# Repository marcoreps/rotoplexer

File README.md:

# rotoplexer
 Nanovolt scanner with rotary switches, first draft for experimentation only

Inspired by
https://dataproof.com/Publications/NBS430.PDF
https://iopscience.iop.org/article/10.1088/0957-0233/24/2/025008

Python software example
https://github.com/marcoreps/multiinstrumentalist/blob/11b641b6d90bda38c73909955b253200de4179e4/main.py#L624

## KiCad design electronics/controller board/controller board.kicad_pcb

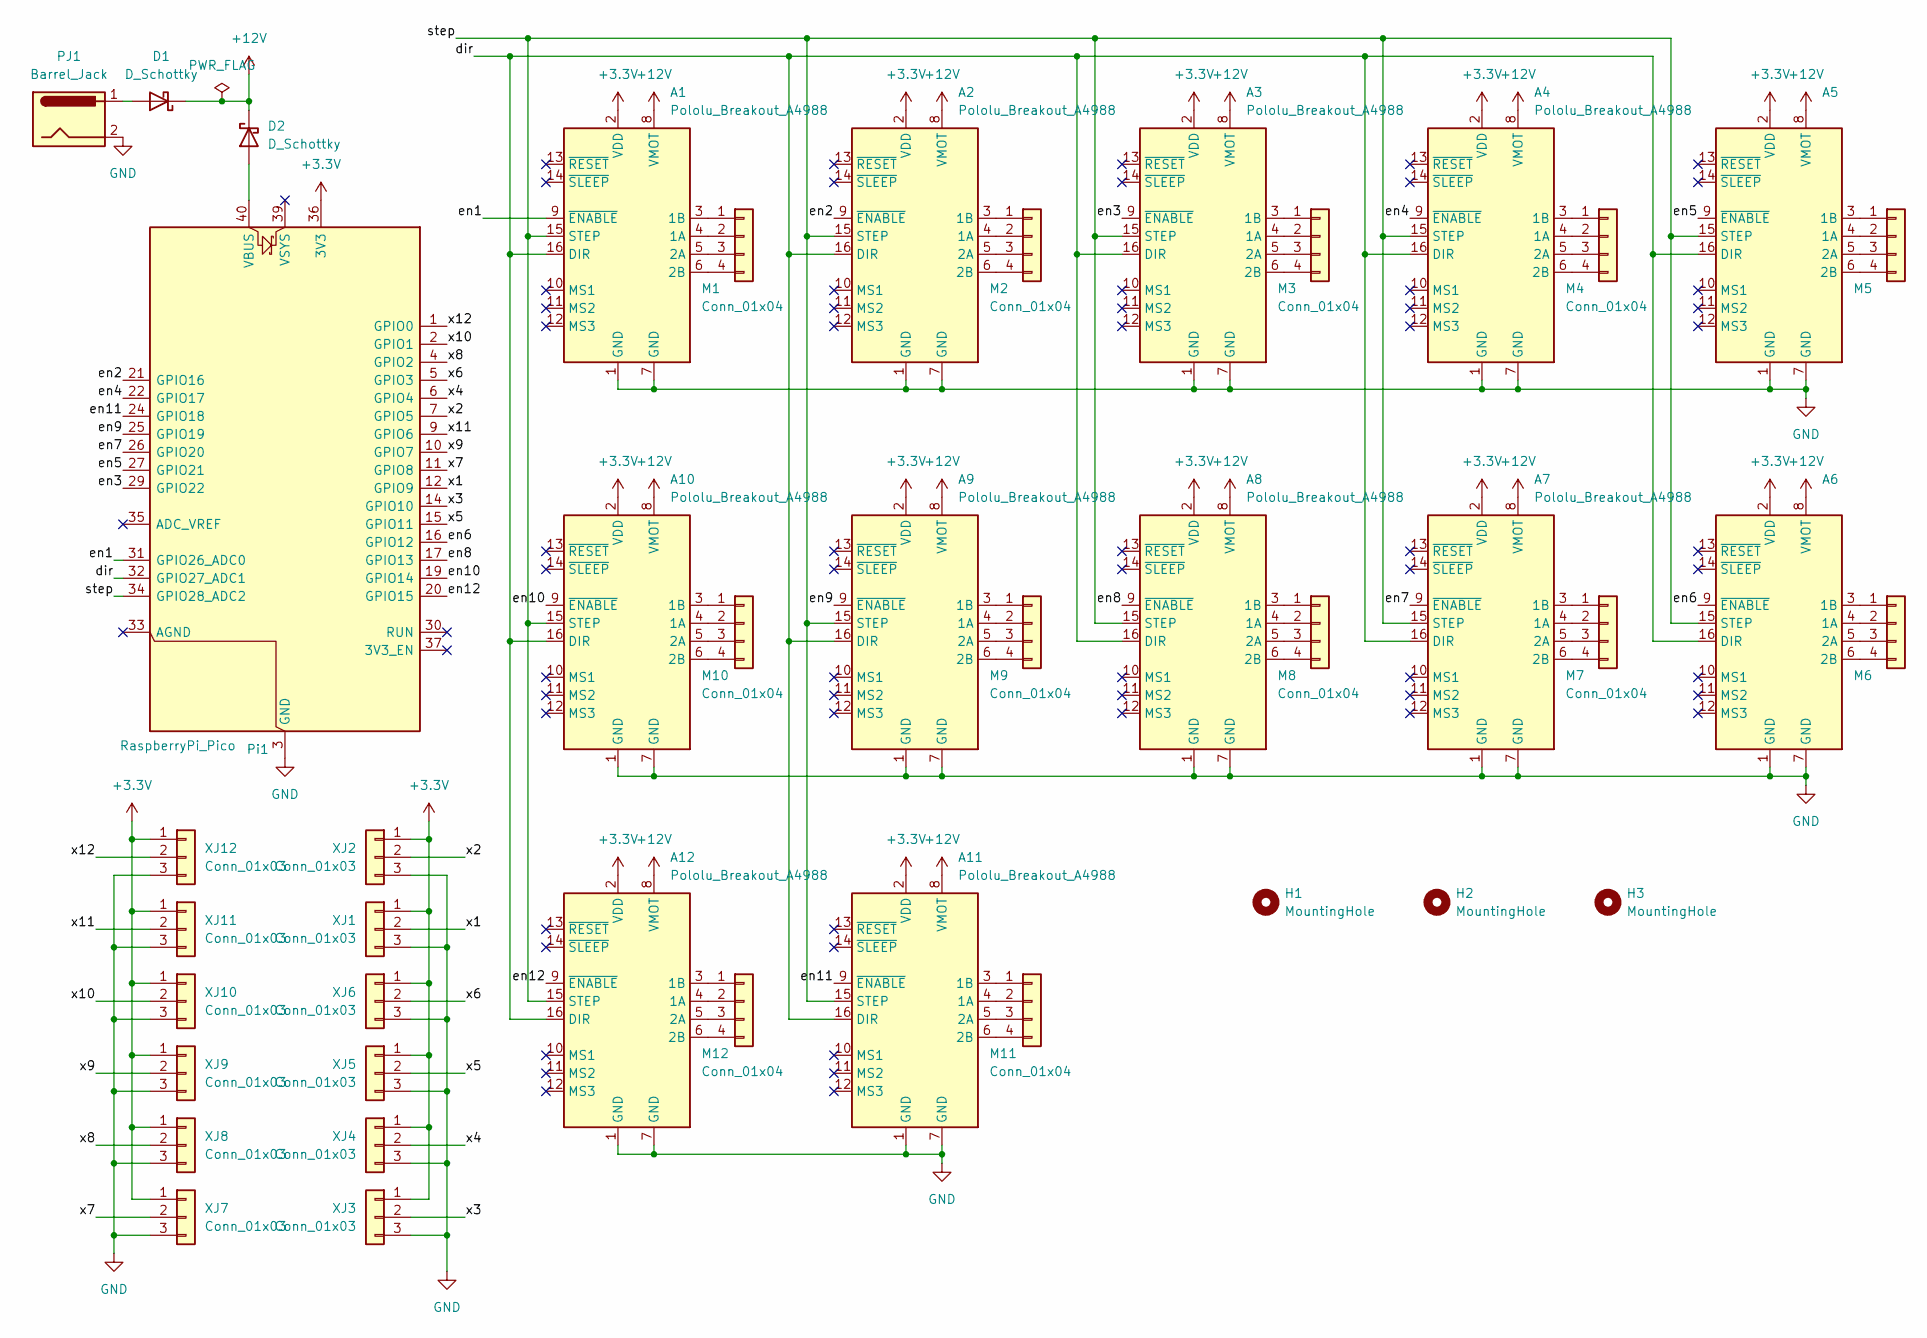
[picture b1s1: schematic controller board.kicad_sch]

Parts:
A1, A2, A3, A4, A5, A6, A7, A8, A9, A10, A11, A12: Pololu_Breakout_A4988; Pololu_Breakout-16_15.2x20.3mm
D1, D2: D_Schottky; D_SMA
H1, H2, H3: MountingHole; MountingHole_3.2mm_M3
M1, M2, M3, M4, M5, M6, M7, M8, M9, M10, M11, M12: Conn_01x04; PinHeader_1x04_P2.54mm_Vertical
PJ1: Barrel_Jack; BarrelJack_CUI_PJ-063AH_Horizontal
Pi1: RaspberryPi_Pico; RaspberryPi_Pico_Common
XJ1, XJ2, XJ3, XJ4, XJ5, XJ6, XJ7, XJ8, XJ9, XJ10, XJ11, XJ12: Conn_01x03; PinHeader_1x03_P2.54mm_Vertical

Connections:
+3.3V: A1.2 (VDD), A2.2 (VDD), A3.2 (VDD), A4.2 (VDD), A5.2 (VDD), A6.2 (VDD), A7.2 (VDD), A8.2 (VDD), A9.2 (VDD), A10.2 (VDD), A11.2 (VDD), A12.2 (VDD), Pi1.36 (3V3), XJ1.1, XJ2.1, XJ3.1, XJ4.1, XJ5.1, XJ6.1, XJ7.1, XJ8.1, XJ9.1, XJ10.1, XJ11.1, XJ12.1
+12V: A1.8 (VMOT), A2.8 (VMOT), A3.8 (VMOT), A4.8 (VMOT), A5.8 (VMOT), A6.8 (VMOT), A7.8 (VMOT), A8.8 (VMOT), A9.8 (VMOT), A10.8 (VMOT), A11.8 (VMOT), A12.8 (VMOT), D1.1 (K), D2.1 (K)
/dir: A1.16 (DIR), A2.16 (DIR), A3.16 (DIR), A4.16 (DIR), A5.16 (DIR), A6.16 (DIR), A7.16 (DIR), A8.16 (DIR), A9.16 (DIR), A10.16 (DIR), A11.16 (DIR), A12.16 (DIR), Pi1.32 (GPIO27_ADC1)
/en1: A1.9 (~ENABLE), Pi1.31 (GPIO26_ADC0)
/en2: A2.9 (~ENABLE), Pi1.21 (GPIO16)
/en3: A3.9 (~ENABLE), Pi1.29 (GPIO22)
/en4: A4.9 (~ENABLE), Pi1.22 (GPIO17)
/en5: A5.9 (~ENABLE), Pi1.27 (GPIO21)
/en6: A6.9 (~ENABLE), Pi1.16 (GPIO12)
/en7: A7.9 (~ENABLE), Pi1.26 (GPIO20)
/en8: A8.9 (~ENABLE), Pi1.17 (GPIO13)
/en9: A9.9 (~ENABLE), Pi1.25 (GPIO19)
/en10: A10.9 (~ENABLE), Pi1.19 (GPIO14)
/en11: A11.9 (~ENABLE), Pi1.24 (GPIO18)
/en12: A12.9 (~ENABLE), Pi1.20 (GPIO15)
/step: A1.15 (STEP), A2.15 (STEP), A3.15 (STEP), A4.15 (STEP), A5.15 (STEP), A6.15 (STEP), A7.15 (STEP), A8.15 (STEP), A9.15 (STEP), A10.15 (STEP), A11.15 (STEP), A12.15 (STEP), Pi1.34 (GPIO28_ADC2)
/x1: Pi1.12 (GPIO9), XJ1.2
/x2: Pi1.7 (GPIO5), XJ2.2
/x3: Pi1.14 (GPIO10), XJ3.2
/x4: Pi1.6 (GPIO4), XJ4.2
/x5: Pi1.15 (GPIO11), XJ5.2
/x6: Pi1.5 (GPIO3), XJ6.2
/x7: Pi1.11 (GPIO8), XJ7.2
/x8: Pi1.4 (GPIO2), XJ8.2
/x9: Pi1.10 (GPIO7), XJ9.2
/x10: Pi1.2 (GPIO1), XJ10.2
/x11: Pi1.9 (GPIO6), XJ11.2
/x12: Pi1.1 (GPIO0), XJ12.2
GND: A1.1 (GND), A1.7 (GND), A2.1 (GND), A2.7 (GND), A3.1 (GND), A3.7 (GND), A4.1 (GND), A4.7 (GND), A5.1 (GND), A5.7 (GND), A6.1 (GND), A6.7 (GND), A7.1 (GND), A7.7 (GND), A8.1 (GND), A8.7 (GND), A9.1 (GND), A9.7 (GND), A10.1 (GND), A10.7 (GND), A11.1 (GND), A11.7 (GND), A12.1 (GND), A12.7 (GND), PJ1.2, Pi1.3 (GND), Pi1.8 (GND), Pi1.13 (GND), Pi1.18 (GND), Pi1.23 (GND), Pi1.28 (GND), Pi1.38 (GND), XJ1.3, XJ2.3, XJ3.3, XJ4.3, XJ5.3, XJ6.3, XJ7.3, XJ8.3, XJ9.3, XJ10.3, XJ11.3, XJ12.3
unnamed: A1.4 (1A), M1.2
unnamed: A1.3 (1B), M1.1
unnamed: A1.5 (2A), M1.3
unnamed: A1.6 (2B), M1.4
unnamed: A2.4 (1A), M2.2
unnamed: A2.3 (1B), M2.1
unnamed: A2.5 (2A), M2.3
unnamed: A2.6 (2B), M2.4
unnamed: A3.4 (1A), M3.2
unnamed: A3.3 (1B), M3.1
unnamed: A3.5 (2A), M3.3
unnamed: A3.6 (2B), M3.4
unnamed: A4.4 (1A), M4.2
unnamed: A4.3 (1B), M4.1
unnamed: A4.5 (2A), M4.3
unnamed: A4.6 (2B), M4.4
unnamed: A5.4 (1A), M5.2
unnamed: A5.3 (1B), M5.1
unnamed: A5.5 (2A), M5.3
unnamed: A5.6 (2B), M5.4
unnamed: A6.4 (1A), M6.2
unnamed: A6.3 (1B), M6.1
unnamed: A6.5 (2A), M6.3
unnamed: A6.6 (2B), M6.4
unnamed: A7.4 (1A), M7.2
unnamed: A7.3 (1B), M7.1
unnamed: A7.5 (2A), M7.3
unnamed: A7.6 (2B), M7.4
unnamed: A8.4 (1A), M8.2
unnamed: A8.3 (1B), M8.1
unnamed: A8.5 (2A), M8.3
unnamed: A8.6 (2B), M8.4
unnamed: A9.4 (1A), M9.2
unnamed: A9.3 (1B), M9.1
unnamed: A9.5 (2A), M9.3
unnamed: A9.6 (2B), M9.4
unnamed: A10.4 (1A), M10.2
unnamed: A10.3 (1B), M10.1
unnamed: A10.5 (2A), M10.3
unnamed: A10.6 (2B), M10.4
unnamed: A11.4 (1A), M11.2
unnamed: A11.3 (1B), M11.1
unnamed: A11.5 (2A), M11.3
unnamed: A11.6 (2B), M11.4
unnamed: A12.4 (1A), M12.2
unnamed: A12.3 (1B), M12.1
unnamed: A12.5 (2A), M12.3
unnamed: A12.6 (2B), M12.4
unnamed: D1.2 (A), PJ1.1
unnamed: D2.2 (A), Pi1.40 (VBUS)

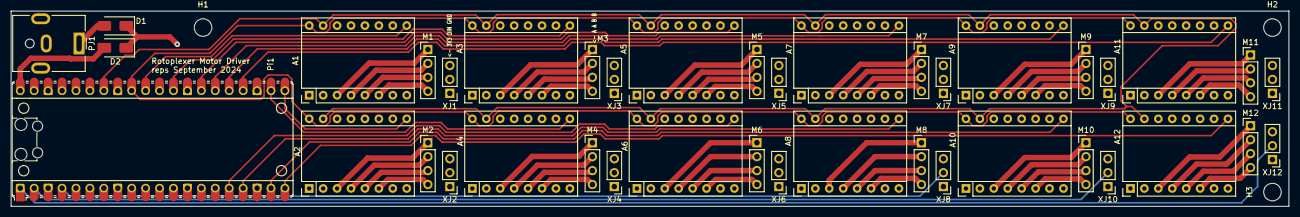
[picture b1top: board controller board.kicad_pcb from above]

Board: 4 copper layers, 233.0 x 35.6 mm, 43 parts (0 on the bottom side), 79 nets.

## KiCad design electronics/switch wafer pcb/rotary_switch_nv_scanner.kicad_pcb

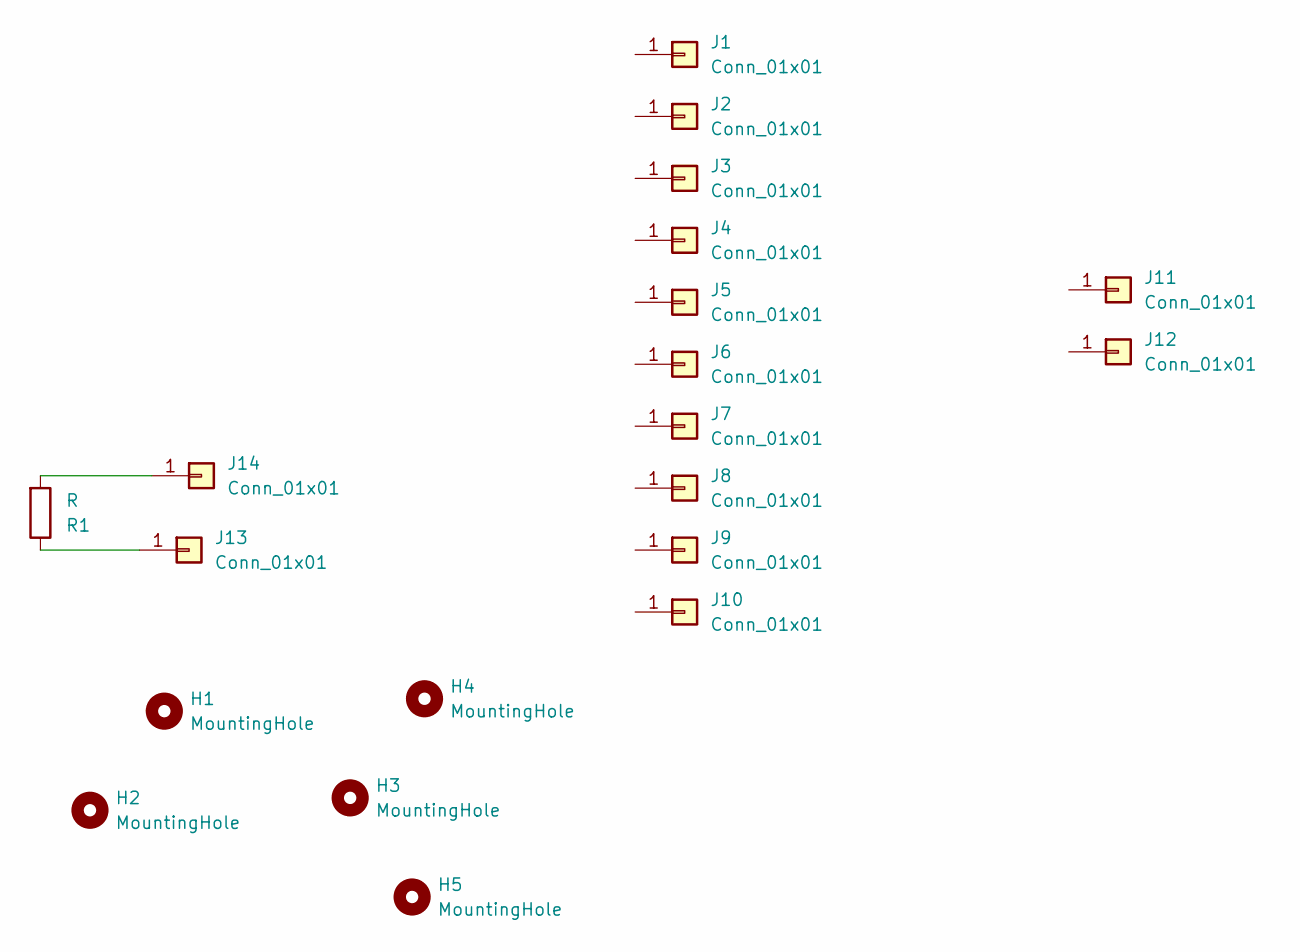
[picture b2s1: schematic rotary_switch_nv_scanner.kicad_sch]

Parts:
H1, H2, H3, H4, H5: MountingHole; MountingHole_3.2mm_M3
J1, J2, J3, J4, J5, J6, J7, J8, J9, J10, J11, J12: Conn_01x01; MountingHole_metal_pcb
J13, J14: Conn_01x01; SolderWirePad_1x01_SMD_1x2mm
R1: R; R_0603_1608Metric

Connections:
unnamed: J13.1, R1.1
unnamed: J14.1, R1.2

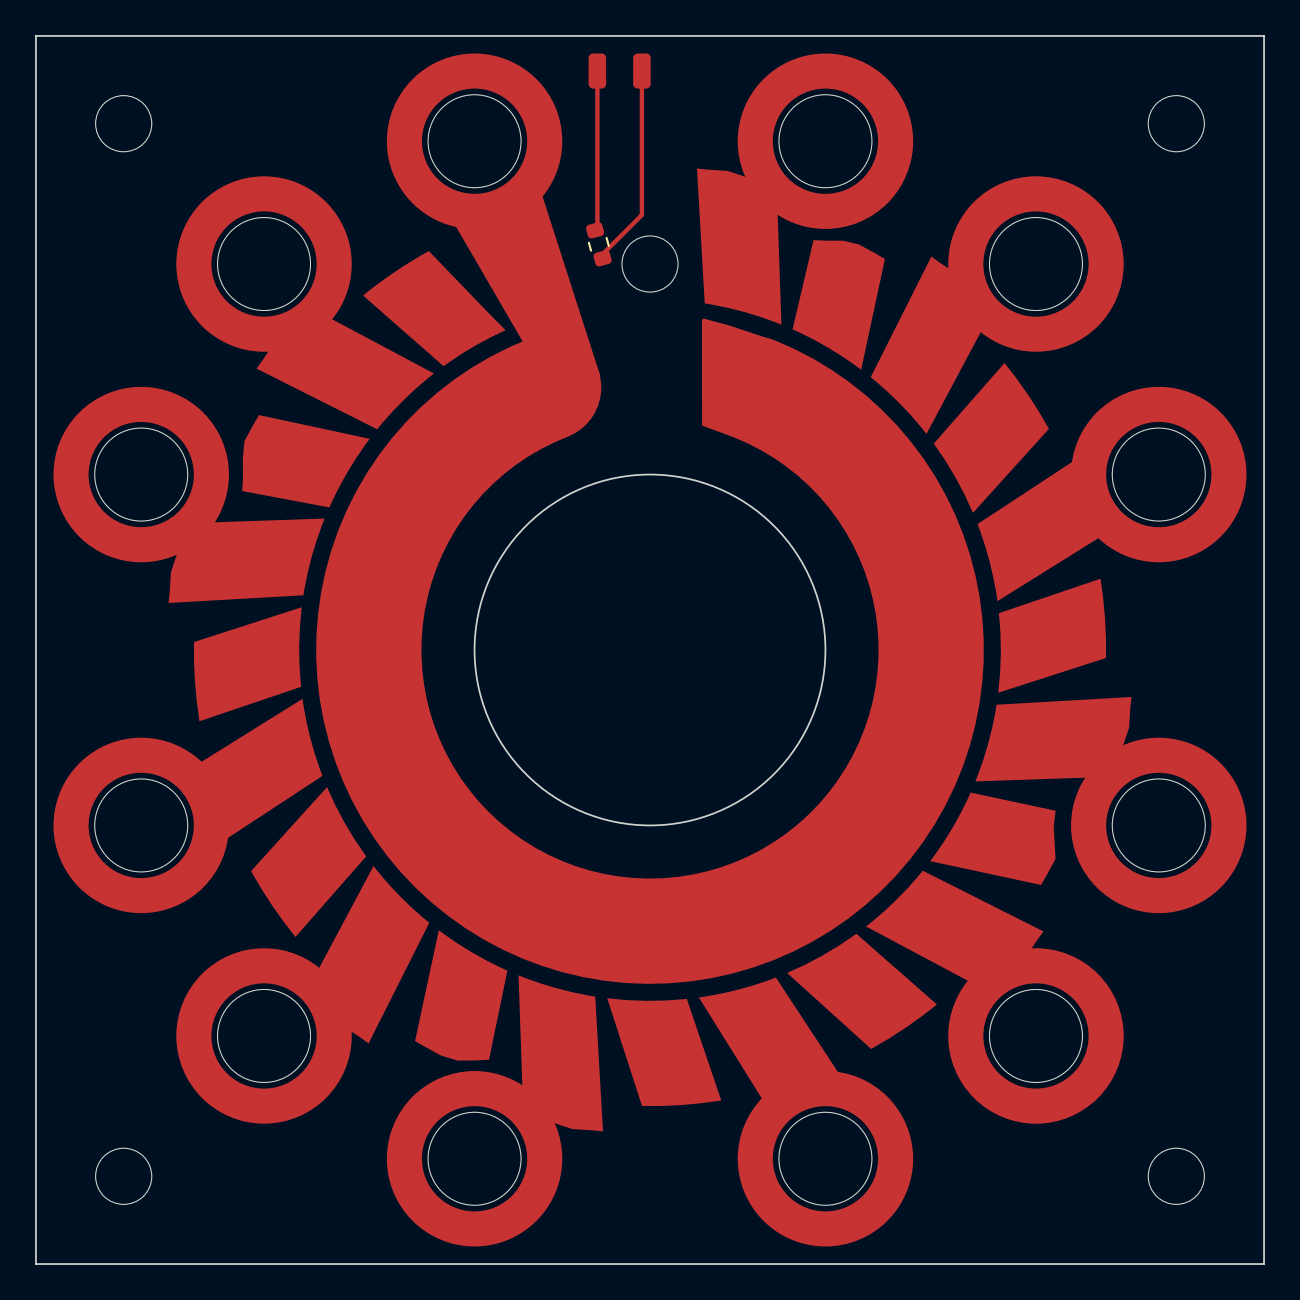
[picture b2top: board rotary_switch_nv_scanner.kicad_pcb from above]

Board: 2 copper layers, 70.0 x 70.0 mm, 20 parts (0 on the bottom side), 2 nets.

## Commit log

2024-05-15 asdf
2024-09-29 new controller board and pi pico firmware for the same
